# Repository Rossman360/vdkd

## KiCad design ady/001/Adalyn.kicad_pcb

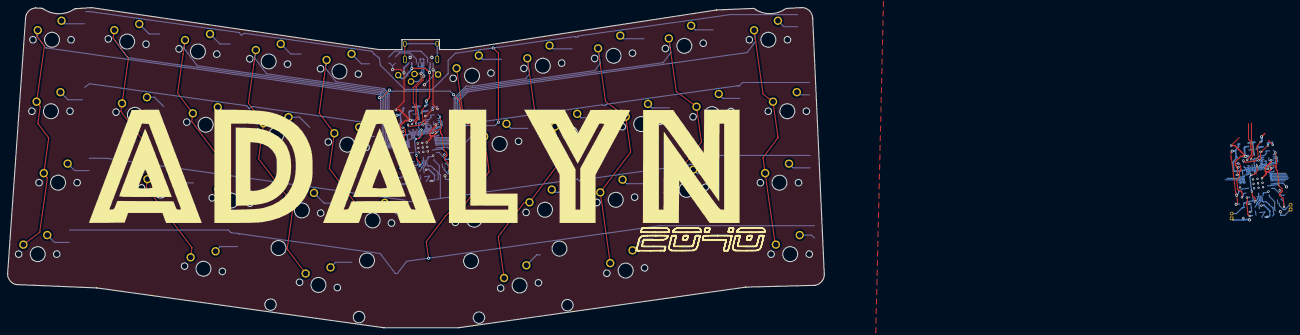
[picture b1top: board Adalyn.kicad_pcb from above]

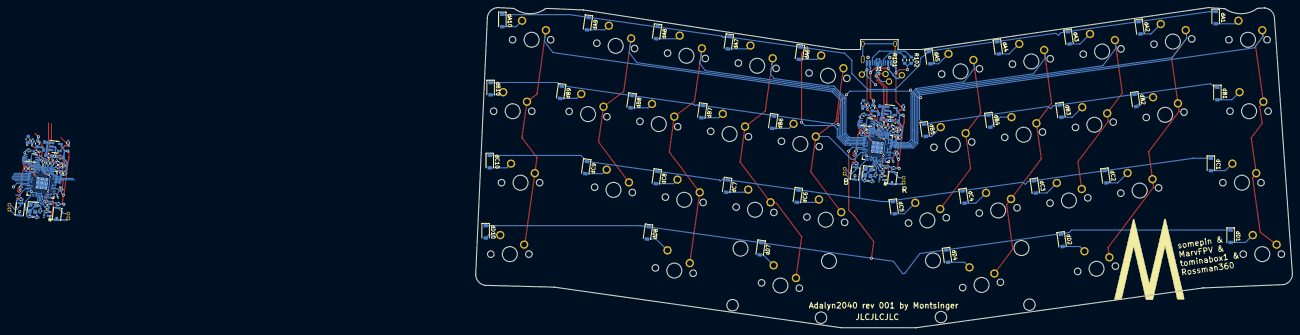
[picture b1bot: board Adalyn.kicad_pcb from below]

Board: 2 copper layers, 217.7 x 85.3 mm, 149 parts (109 on the bottom side), 89 nets.

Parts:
C1, C1#2, C2, C2#2: 1µ; C_0603_1608Metric
C3, C3#2, C4, C4#2: 15p; C_0402_1005Metric
C5, C5#2, C6, C6#2: 1µ; C_0402_1005Metric
C7, C7#2, C8, C8#2, C9, C9#2, C10, C10#2, C11, C11#2, C12, C12#2, C13, C13#2, C14, C14#2: 100n; C_0402_1005Metric
D1, D1#2: LED; LED_0402_1005Metric
D2, D2#2: B5817; D_SOD-323
F1, F1#2: Polyfuse; Fuse_0603_1608Metric
FB1, FB1#2: FerriteBead_Small; L_0603_1608Metric
J1: HRO-TYPE-C-31-M-12; HRO-TYPE-C-31-M-12-Assembly
J5, J5#2, J5#3, J5#4: Conn_01x02; PinHeader_1x02_P1.27mm_Vertical
R1, R1#2, R3, R3#2, R8, R8#2: 1k; R_0402_1005Metric
R2, R2#2, R9, R9#2, R11, R11#2: 10k; R_0402_1005Metric
R4, R4#2, R5, R5#2, R10, R10#2: 5.1k; R_0402_1005Metric
R6, R6#2, R7, R7#2: 27; R_0402_1005Metric
R101, R102: 5.1k; R_0603_1608Metric
SW1, SW1#2, SW2, SW2#2: SW_Push; SW_SPST_CK_KXT3
U1, U1#2: RP2040; QFN-56-1EP_7x7mm_P0.4mm_EP3.2x3.2mm
U2: GD25Q80CEIGR; USON-8-1EP_3x2mm_P0.5mm_EP0.25x1.65mm
U2#2: GD25Q80CEIGR; flash-chip
U3, U3#2: XC6210B332MR-G; SOT-23-5
Y1, Y1#2: Crystal_GND24; Crystal_SMD_2520-4Pin_2.5x2.0mm
dA1, dA2, dA3, dA4, dA5, dA6, dA7, dA8, dA9, dA10: Diode; diode_smd
dB1, dB2, dB3, dB4, dB5, dB6, dB7, dB8, dB9, dB10: Diode; diode_smd
dC1, dC2, dC3, dC4, dC5, dC6, dC7, dC8, dC9, dC10: Diode; diode_smd
dD1, dD2, dD4, dD7, dD8, dD10: Diode; diode_smd
kA1, kA2, kA3, kA4, kA5, kA6, kA7, kA8, kA9, kA10: MX-NoLED; MXOnly-1U-NoLED
kB1, kB2, kB3, kB4, kB5, kB6, kB7, kB8, kB9, kB10: MX-NoLED; MXOnly-1U-NoLED
kC1, kC2, kC3, kC4, kC5, kC6, kC7, kC8, kC9, kC10: MX-NoLED; MXOnly-1U-NoLED
kD1, kD2, kD8, kD10: MX-NoLED; MXOnly-1U-NoLED
kD4: MX-NoLED; MXOnly-2.25U-ReversedStabilizers-NoLED
kD7: MX-NoLED; MXOnly-2U-ReversedStabilizers-NoLED

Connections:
+1V1: C6.1, C6#2.1, C7.1, C7#2.1, C8.1, C8#2.1, U1.23 (DVDD), U1.45 (VREG_VOUT), U1.50 (DVDD), U1#2.23 (DVDD), U1#2.45 (VREG_VOUT), U1#2.50 (DVDD)
+3V3: C2.1, C2#2.1, C5.1, C5#2.1, C9.1, C9#2.1, C10.1, C10#2.1, C11.1, C11#2.1, C12.1, C12#2.1, C13.1, C13#2.1, C14.1, C14#2.1, R2.2, R2#2.2, R9.2, R9#2.2, U1.1 (IOVDD), U1.10 (IOVDD), U1.22 (IOVDD), U1.33 (IOVDD), U1.42 (IOVDD), U1.43 (ADC_AVDD), U1.44 (VREG_IN), U1.48 (USB_VDD), U1.49 (IOVDD), U1#2.1 (IOVDD), U1#2.10 (IOVDD), U1#2.22 (IOVDD), U1#2.33 (IOVDD), U1#2.42 (IOVDD), U1#2.43 (ADC_AVDD), U1#2.44 (VREG_IN), U1#2.48 (USB_VDD), U1#2.49 (IOVDD), U2.8 (VCC), U2#2.8 (VCC), U3.5 (VOUT), U3#2.5 (VOUT)
+5V: C1.1, C1#2.1, D2.1 (K), D2#2.1 (K), U3.1 (VIN), U3.3 (EN), U3#2.1 (VIN), U3#2.3 (EN)
/D6: U1.8 (GPIO6), U1#2.8 (GPIO6)
/D8: U1.11 (GPIO8), U1#2.11 (GPIO8)
/D13: U1.16 (GPIO13), U1#2.16 (GPIO13)
/D14: U1.17 (GPIO14), U1#2.17 (GPIO14)
/D15: U1.18 (GPIO15), U1#2.18 (GPIO15)
/D16: U1.27 (GPIO16), U1#2.27 (GPIO16)
/D21: U1.32 (GPIO21), U1#2.32 (GPIO21)
/LED: D1.2 (A), D1#2.2 (A), U1.28 (GPIO17), U1#2.28 (GPIO17)
/MISO: U1.31 (GPIO20), U1#2.31 (GPIO20)
/MOSI: U1.35 (GPIO23), U1#2.35 (GPIO23)
/QSPI_D0: U1.53 (QSPI_SD0), U1#2.53 (QSPI_SD0), U2.5 (DI(IO0)), U2#2.5 (DI(IO0))
/QSPI_D1: U1.55 (QSPI_SD1), U1#2.55 (QSPI_SD1), U2.2 (DO(IO1)), U2#2.2 (DO(IO1))
/QSPI_D2: U1.54 (QSPI_SD2), U1#2.54 (QSPI_SD2), U2.3 (IO2), U2#2.3 (IO2)
/QSPI_D3: U1.51 (QSPI_SD3), U1#2.51 (QSPI_SD3), U2.7 (IO3), U2#2.7 (IO3)
/QSPI_SCLK: U1.52 (QSPI_SCLK), U1#2.52 (QSPI_SCLK), U2.6 (CLK), U2#2.6 (CLK)
/QSPI_~CS: R3.2, R3#2.2, R9.1, R9#2.1, U1.56 (QSPI_SS), U1#2.56 (QSPI_SS), U2.1 (~CS), U2#2.1 (~CS)
/SCLK: U1.34 (GPIO22), U1#2.34 (GPIO22)
/VBUS_DET: R10.1, R10#2.1, R11.2, R11#2.2, U1.30 (GPIO19), U1#2.30 (GPIO19)
/~RESET: J5.2, J5#2.2, R2.1, R2#2.1, SW1.2, SW1#2.2, U1.26 (RUN/~RST), U1#2.26 (RUN/~RST)
CC1: J1.4, R101.2
CC2: J1.10, R102.1
D+: J1.6, J1.8, R6.1, R6#2.1
D-: J1.5, J1.7, R7.1, R7#2.1
GND: C1.2, C1#2.2, C2.2, C2#2.2, C3.2, C3#2.2, C4.2, C4#2.2, C5.2, C5#2.2, C6.2, C6#2.2, C7.2, C7#2.2, C8.2, C8#2.2, C9.2, C9#2.2, C10.2, C10#2.2, C11.2, C11#2.2, C12.2, C12#2.2, C13.2, C13#2.2, C14.2, C14#2.2, FB1.1, FB1#2.1, J1.1, J1.12, J5.1, J5#2.1, J5#3.1, J5#4.1, R1.1, R1#2.1, R4.2, R4#2.2, R5.2, R5#2.2, R11.1, R11#2.1, R101.1, R102.2, SW1.1, SW1#2.1, SW2.1, SW2#2.1, U1.19 (TESTEN), U1.57 (GND), U1#2.19 (TESTEN), U1#2.57 (GND), U2.4 (GND), U2.9 (EP), U2#2.4 (GND), U2#2.9 (EP), U3.2 (GND), U3#2.2 (GND), Y1.2, Y1.4, Y1#2.2, Y1#2.4
unnamed: C4.1, C4#2.1, R8.1, R8#2.1, Y1.3, Y1#2.3
unnamed: D1.1 (K), D1#2.1 (K), R1.2, R1#2.2
unnamed: D2.2 (A), D2#2.2 (A), F1.2, F1#2.2
unnamed: R4.1, R4#2.1
unnamed: R5.1, R5#2.1
unnamed: FB1.2, FB1#2.2
unnamed: J5#3.2, J5#4.2, R3.1, R3#2.1, SW2.2, SW2#2.2
unnamed: R7.2, R7#2.2, U1.46 (USB_DM), U1#2.46 (USB_DM)
unnamed: R6.2, R6#2.2, U1.47 (USB_DP), U1#2.47 (USB_DP)
unnamed: C3.1, C3#2.1, U1.20 (XIN), U1#2.20 (XIN), Y1.1, Y1#2.1
unnamed: R8.2, R8#2.2, U1.21 (XOUT), U1#2.21 (XOUT)
unnamed: dA1.2 (A), kA1.2 (ROW)
unnamed: dA2.2 (A), kA2.2 (ROW)
unnamed: dA3.2 (A), kA3.2 (ROW)
unnamed: dA4.2 (A), kA4.2 (ROW)
unnamed: dA5.2 (A), kA5.2 (ROW)
unnamed: dA6.2 (A), kA6.2 (ROW)
unnamed: dA7.2 (A), kA7.2 (ROW)
unnamed: dA8.2 (A), kA8.2 (ROW)
unnamed: dA9.2 (A), kA9.2 (ROW)
unnamed: dA10.2 (A), kA10.2 (ROW)
unnamed: dB1.2 (A), kB1.2 (ROW)
unnamed: dB2.2 (A), kB2.2 (ROW)
unnamed: dB3.2 (A), kB3.2 (ROW)
unnamed: dB4.2 (A), kB4.2 (ROW)
unnamed: dB5.2 (A), kB5.2 (ROW)
unnamed: dB6.2 (A), kB6.2 (ROW)
unnamed: dB7.2 (A), kB7.2 (ROW)
unnamed: dB8.2 (A), kB8.2 (ROW)
unnamed: dB9.2 (A), kB9.2 (ROW)
unnamed: dB10.2 (A), kB10.2 (ROW)
unnamed: dC1.2 (A), kC1.2 (ROW)
unnamed: dC2.2 (A), kC2.2 (ROW)
unnamed: dC3.2 (A), kC3.2 (ROW)
unnamed: dC4.2 (A), kC4.2 (ROW)
unnamed: dC5.2 (A), kC5.2 (ROW)
unnamed: dC6.2 (A), kC6.2 (ROW)
unnamed: dC7.2 (A), kC7.2 (ROW)
unnamed: dC8.2 (A), kC8.2 (ROW)
unnamed: dC9.2 (A), kC9.2 (ROW)
unnamed: dC10.2 (A), kC10.2 (ROW)
unnamed: dD1.2 (A), kD1.2 (ROW)
unnamed: dD2.2 (A), kD2.2 (ROW)
unnamed: dD4.2 (A), kD4.2
unnamed: dD7.2 (A), kD7.2
unnamed: dD8.2 (A), kD8.2 (ROW)
unnamed: dD10.2 (A), kD10.2 (ROW)
VBUS: F1.1, F1#2.1, J1.2, J1.11, R10.2, R10#2.2
c1: U1.37 (GPIO25), U1#2.37 (GPIO25), kA1.1 (COL), kB1.1 (COL), kC1.1 (COL), kD1.1 (COL)
c2: U1.38 (GPIO26_ADC0), U1#2.38 (GPIO26_ADC0), kA2.1 (COL), kB2.1 (COL), kC2.1 (COL), kD2.1 (COL)
c3: U1.39 (GPIO27_ADC1), U1#2.39 (GPIO27_ADC1), kA3.1 (COL), kB3.1 (COL), kC3.1 (COL)
c4: U1.40 (GPIO28_ADC2), U1#2.40 (GPIO28_ADC2), kA4.1 (COL), kB4.1 (COL), kC4.1 (COL), kD4.1
c5: U1.41 (GPIO29_ADC3), U1#2.41 (GPIO29_ADC3), kA5.1 (COL), kB5.1 (COL), kC5.1 (COL)
c6: U1.12 (GPIO9), U1#2.12 (GPIO9), kA6.1 (COL), kB6.1 (COL), kC6.1 (COL)
c7: U1.2 (GPIO0), U1#2.2 (GPIO0), kA7.1 (COL), kB7.1 (COL), kC7.1 (COL), kD7.1
c8: U1.3 (GPIO1), U1#2.3 (GPIO1), kA8.1 (COL), kB8.1 (COL), kC8.1 (COL), kD8.1 (COL)
c9: U1.4 (GPIO2), U1#2.4 (GPIO2), kA9.1 (COL), kB9.1 (COL), kC9.1 (COL)
c10: U1.5 (GPIO3), U1#2.5 (GPIO3), kA10.1 (COL), kB10.1 (COL), kC10.1 (COL), kD10.1 (COL)
rA: U1.7 (GPIO5), U1#2.7 (GPIO5), dA1.1 (K), dA2.1 (K), dA3.1 (K), dA4.1 (K), dA5.1 (K), dA6.1 (K), dA7.1 (K), dA8.1 (K), dA9.1 (K), dA10.1 (K)
rB: U1.6 (GPIO4), U1#2.6 (GPIO4), dB1.1 (K), dB2.1 (K), dB3.1 (K), dB4.1 (K), dB5.1 (K), dB6.1 (K), dB7.1 (K), dB8.1 (K), dB9.1 (K), dB10.1 (K)
rC: U1.15 (GPIO12), U1#2.15 (GPIO12), dC1.1 (K), dC2.1 (K), dC3.1 (K), dC4.1 (K), dC5.1 (K), dC6.1 (K), dC7.1 (K), dC8.1 (K), dC9.1 (K), dC10.1 (K)
rD: U1.9 (GPIO7), U1#2.9 (GPIO7), dD1.1 (K), dD2.1 (K), dD4.1 (K), dD7.1 (K), dD8.1 (K), dD10.1 (K)

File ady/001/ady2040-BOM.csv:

Comment,Designator,Footprint,LCSC
51k,"R101,R102",R_0603_1608Metric,2,5.1k,~
diodes,"dC6,dB10,dA6,dB8,dC10,dB4,dA10,dD1,dC5,dC2,dD2,dC1,dD4,dB3,dD8,dC4,dA3,dC3,dC7,dB1,dB7,dA7,dA4,dB6,dB5,dA8,dC8,dD7,dA2,dA9,dC9,dA1,dA5,dD10,dB9,dB2",C64898,
usb,J1,HRO-TYPE-C-31-M-12-Assembly,C165948,~
1k,"R1,R3,R8",R_0402_1005Metric,C11702,~
B5817,D2,D_SOD-323,C123899
LED,D1,LED_0402_1005Metric,C130719
100n,"C10,C11,C12,C13,C14,C7,C8,C9",C_0402_1005Metric,C1525
15p,"C3,C4",C_0402_1005Metric,C1548
1µ,"C1,C2",C_0603_1608Metric,C19666
RP2040,U1,QFN-56-1EP_7x7mm_P0.4mm_EP3.2x3.2mm,C2040
Crystal_GND24,Y1,Crystal_SMD_2520-4Pin_2.5x2.0mm,C2149204
27,"R6,R7",R_0402_1005Metric,C25100
10k,"R11,R2,R9",R_0402_1005Metric,C25744
5.1k,"R10,R4,R5",R_0402_1005Metric,C25905
SW_Push,"SW1,SW2",SW_SPST_CK_KXT3,C319433
GD25Q80CEIGR,U2,USON-8-1EP_3x2mm_P0.5mm_EP0.25x1.65mm,C152596
1µ,"C5,C6",C_0402_1005Metric,C52923
Polyfuse,F1,Fuse_0603_1608Metric,C69679
XC6210B332MR-G,U3,SOT-23-5,C82942
FerriteBead_Small,FB1,L_0603_1608Metric,C98288

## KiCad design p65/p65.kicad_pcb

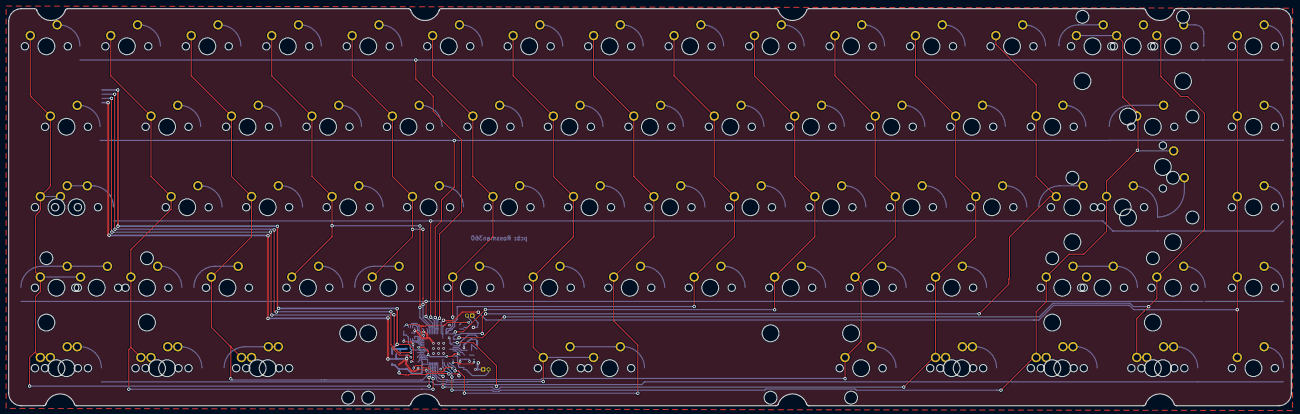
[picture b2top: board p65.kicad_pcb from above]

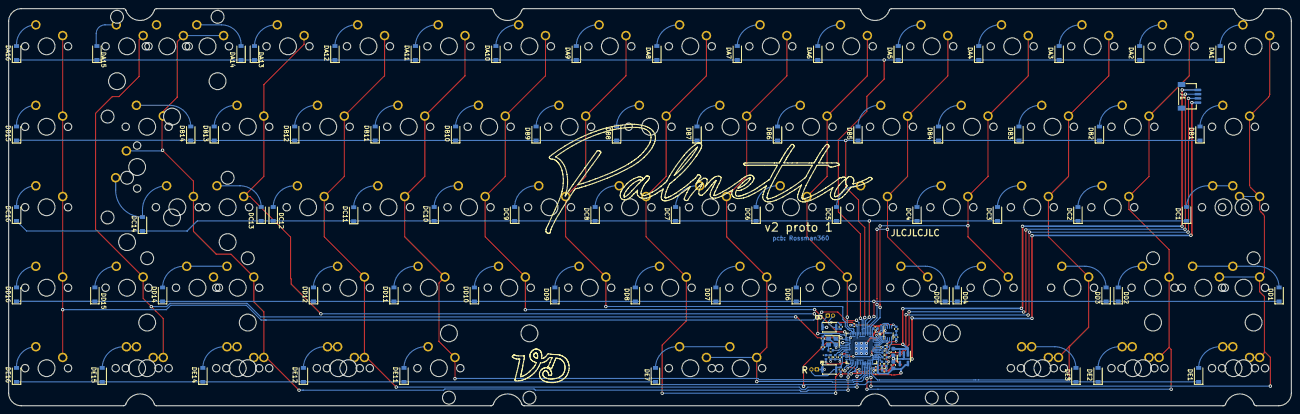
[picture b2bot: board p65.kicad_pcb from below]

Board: 2 copper layers, 303.7 x 94.0 mm, 185 parts (101 on the bottom side), 113 nets.

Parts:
C1, C2: 1µ; C_0603_1608Metric
C3, C4: 15p; C_0402_1005Metric
C5, C6: 1µ; C_0402_1005Metric
C7, C8, C9, C10, C11, C12, C13, C14: 100n; C_0402_1005Metric
D1: LED; LED_0402_1005Metric
DA1, DA2, DA3, DA4, DA5, DA6, DA7, DA8, DA9, DA10, DA11, DA12, DA13, DA14, DA15, DA16: Diode; diode_smd
DB1, DB2, DB3, DB4, DB5, DB6, DB7, DB8, DB9, DB10, DB11, DB12, DB13, DB14, DB15: Diode; diode_smd
DC1, DC2, DC3, DC4, DC5, DC6, DC7, DC8, DC9, DC10, DC11, DC12, DC13, DC14, DC16: Diode; diode_smd
DD1, DD2, DD3, DD4, DD5, DD6, DD7, DD8, DD9, DD10, DD11, DD12, DD14, DD15, DD16: Diode; diode_smd
DE1, DE2, DE3, DE7, DE11, DE12, DE14, DE15, DE16: Diode; diode_smd
J1: SM04B-SRSS-TB(LF)(SN); jst
J5, J5#2: Conn_01x02; PinHeader_1x02_P1.27mm_Vertical
KA1: Esc; MXOnly-1U-NoLED
KA2: 1; MXOnly-1U-NoLED
KA3: 2; MXOnly-1U-NoLED
KA4: 3; MXOnly-1U-NoLED
KA5: 4; MXOnly-1U-NoLED
KA6: 5; MXOnly-1U-NoLED
KA7: 6; MXOnly-1U-NoLED
KA8: 7; MXOnly-1U-NoLED
KA9: 8; MXOnly-1U-NoLED
KA10: 9; MXOnly-1U-NoLED
KA11: 10; MXOnly-1U-NoLED
KA12: -; MXOnly-1U-NoLED
KA13: =; MXOnly-1U-NoLED
KA14: Bspc; MXOnly-1U-NoLED
KA14.2: Bspc; MXOnly-2U-NoLED
KA15: `; MXOnly-1U-NoLED
KA16: del; MXOnly-1U-NoLED
KB1: Tab; MXOnly-1.5U-NoLED
KB2: Q; MXOnly-1U-NoLED
KB3: W; MXOnly-1U-NoLED
KB4: E; MXOnly-1U-NoLED
KB5: R; MXOnly-1U-NoLED
KB6: T; MXOnly-1U-NoLED
KB7: Y; MXOnly-1U-NoLED
KB8: U; MXOnly-1U-NoLED
KB9: I; MXOnly-1U-NoLED
KB10: O; MXOnly-1U-NoLED
KB11: P; MXOnly-1U-NoLED
KB12: [; MXOnly-1U-NoLED
KB13: ]; MXOnly-1U-NoLED
KB14: \; MXOnly-1.5U-NoLED
KB16: home; MXOnly-1U-NoLED
KC1: Caps; MXOnly-1.75U-NoLED
KC1.2: Stepped; MXOnly-1.25U-NoLED
KC2: A; MXOnly-1U-NoLED
KC3: S; MXOnly-1U-NoLED
KC4: D; MXOnly-1U-NoLED
KC5: F; MXOnly-1U-NoLED
KC6: G; MXOnly-1U-NoLED
KC7: H; MXOnly-1U-NoLED
KC8: J; MXOnly-1U-NoLED
KC9: K; MXOnly-1U-NoLED
KC10: L; MXOnly-1U-NoLED
KC11: ;; MXOnly-1U-NoLED
KC12: '; MXOnly-1U-NoLED
KC13: #; MXOnly-1U-NoLED
KC14: Enter; MXOnly-2.25U-NoLED
KC14.2: Enter; MXOnly-ISO-ROTATED-ReversedStabilizers-NoLED
KC16: pgup; MXOnly-1U-NoLED
KD1: Lshift; MXOnly-1.25U-NoLED
KD1.2: Lshift; MXOnly-2.25U-NoLED
KD2: \; MXOnly-1U-NoLED
KD3: Z; MXOnly-1U-NoLED
KD4: X; MXOnly-1U-NoLED
KD5: C; MXOnly-1U-NoLED
KD6: V; MXOnly-1U-NoLED
KD7: B; MXOnly-1U-NoLED
KD8: N; MXOnly-1U-NoLED
KD9: M; MXOnly-1U-NoLED
KD10: ,; MXOnly-1U-NoLED
KD11: .; MXOnly-1U-NoLED
KD12: /; MXOnly-1U-NoLED
KD14: Rsft; MXOnly-1.75U-NoLED
KD14.2: Rsft; MXOnly-2.75U-NoLED
KD15: Fn; MXOnly-1U-NoLED
KD16: pgdn; MXOnly-1U-NoLED
KE1: LCtl; MXOnly-1.25U-NoLED
KE1.2: LCtl; MXOnly-1.5U-NoLED
KE2: LWin; MXOnly-1.25U-NoLED
KE2.2: LWin; MXOnly-1U-NoLED
KE3: LAlt; MXOnly-1.25U-NoLED
KE3.2: LAlt; MXOnly-1.5U-NoLED
KE7: Space; MXOnly-6.25U-ReversedStabilizers-NoLED
KE7.2: Space; MXOnly-7U-ReversedStabilizers-NoLED
KE11: AltGr; MXOnly-1.25U-NoLED
KE12: Rwin; MXOnly-1.25U-NoLED
KE12.2: Rwin; MXOnly-1.5U-NoLED
KE14: RMenu; MXOnly-1.25U-NoLED
KE14.2: RMenu; MXOnly-1U-NoLED
KE15: Rctl; MXOnly-1.25U-NoLED
KE15.2: Rctl; MXOnly-1.5U-NoLED
KE16: Pgdn; MXOnly-1U-NoLED
R1, R3, R8: 1k; R_0402_1005Metric
R2, R9, R11: 10k; R_0402_1005Metric
R6, R7: 27; R_0402_1005Metric
R10: 5.1k; R_0402_1005Metric
SW1, SW2: SW_Push; SW_SPST_CK_KXT3
U1: RP2040; QFN-56-1EP_7x7mm_P0.4mm_EP3.2x3.2mm
U2: GD25Q80CEIGR; USON-8-1EP_3x2mm_P0.5mm_EP0.25x1.65mm
U3: XC6210B332MR-G; SOT-23-5
Y1: Crystal_GND24; Crystal_SMD_2520-4Pin_2.5x2.0mm

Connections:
+1V1: C6.1, C7.1, C8.1, U1.23 (DVDD), U1.45 (VREG_VOUT), U1.50 (DVDD)
+3V3: C2.1, C5.1, C9.1, C10.1, C11.1, C12.1, C13.1, C14.1, R2.2, R9.2, U1.1 (IOVDD), U1.10 (IOVDD), U1.22 (IOVDD), U1.33 (IOVDD), U1.42 (IOVDD), U1.43 (ADC_AVDD), U1.44 (VREG_IN), U1.48 (USB_VDD), U1.49 (IOVDD), U2.8 (VCC), U3.5 (VOUT)
+5V: C1.1, J1.1, R10.2, U3.1 (VIN), U3.3 (EN)
/LED: D1.2 (A), U1.28 (GPIO17)
/QSPI_D0: U1.53 (QSPI_SD0), U2.5 (DI(IO0))
/QSPI_D1: U1.55 (QSPI_SD1), U2.2 (DO(IO1))
/QSPI_D2: U1.54 (QSPI_SD2), U2.3 (IO2)
/QSPI_D3: U1.51 (QSPI_SD3), U2.7 (IO3)
/QSPI_SCLK: U1.52 (QSPI_SCLK), U2.6 (CLK)
/QSPI_~CS: R3.2, R9.1, U1.56 (QSPI_SS), U2.1 (~CS)
/VBUS_DET: R10.1, R11.2, U1.30 (GPIO19)
/~RESET: R2.1, SW1.2, U1.26 (RUN/~RST)
D+: J1.3, R6.1
D-: J1.2, R7.1
GND: C1.2, C2.2, C3.2, C4.2, C5.2, C6.2, C7.2, C8.2, C9.2, C10.2, C11.2, C12.2, C13.2, C14.2, J1.4, J5.1, J5#2.1, R1.1, R11.1, SW1.1, SW2.1, U1.19 (TESTEN), U1.57 (GND), U2.4 (GND), U2.9 (EP), U3.2 (GND), Y1.2, Y1.4
unnamed: C4.1, R8.1, Y1.3
unnamed: D1.1 (K), R1.2
unnamed: DA1.2 (A), KA1.2 (Row)
unnamed: DA2.2 (A), KA2.2 (Row)
unnamed: DA3.2 (A), KA3.2 (Row)
unnamed: DA4.2 (A), KA4.2 (Row)
unnamed: DA5.2 (A), KA5.2 (Row)
unnamed: DA6.2 (A), KA6.2 (Row)
unnamed: DA7.2 (A), KA7.2 (Row)
unnamed: DA8.2 (A), KA8.2 (Row)
unnamed: DA9.2 (A), KA9.2 (Row)
unnamed: DA10.2 (A), KA10.2 (Row)
unnamed: DA11.2 (A), KA11.2 (Row)
unnamed: DA12.2 (A), KA12.2 (Row)
unnamed: DA13.2 (A), KA13.2 (Row)
unnamed: DA14.2 (A), KA14.2 (Row), KA14.2.2 (Row)
unnamed: DA15.2 (A), KA15.2 (Row)
unnamed: DA16.2 (A), KA16.2 (Row)
unnamed: DB1.2 (A), KB1.2 (Row)
unnamed: DB2.2 (A), KB2.2 (Row)
unnamed: DB3.2 (A), KB3.2 (Row)
unnamed: DB4.2 (A), KB4.2 (Row)
unnamed: DB5.2 (A), KB5.2 (Row)
unnamed: DB6.2 (A), KB6.2 (Row)
unnamed: DB7.2 (A), KB7.2 (Row)
unnamed: DB8.2 (A), KB8.2 (Row)
unnamed: DB9.2 (A), KB9.2 (Row)
unnamed: DB10.2 (A), KB10.2 (Row)
unnamed: DB11.2 (A), KB11.2 (Row)
unnamed: DB12.2 (A), KB12.2 (Row)
unnamed: DB13.2 (A), KB13.2 (Row)
unnamed: DB14.2 (A), KB14.2 (Row)
unnamed: DB15.2 (A), KB16.2 (Row)
unnamed: DC1.2 (A), KC1.2 (Row), KC1.2.2 (Row)
unnamed: DC2.2 (A), KC2.2 (Row)
unnamed: DC3.2 (A), KC3.2 (Row)
unnamed: DC4.2 (A), KC4.2 (Row)
unnamed: DC5.2 (A), KC5.2 (Row)
unnamed: DC6.2 (A), KC6.2 (Row)
unnamed: DC7.2 (A), KC7.2 (Row)
unnamed: DC8.2 (A), KC8.2 (Row)
unnamed: DC9.2 (A), KC9.2 (Row)
unnamed: DC10.2 (A), KC10.2 (Row)
unnamed: DC11.2 (A), KC11.2 (Row)
unnamed: DC12.2 (A), KC12.2 (Row)
unnamed: DC13.2 (A), KC13.2 (Row)
unnamed: DC14.2 (A), KC14.2 (Row), KC14.2.2 (Row)
unnamed: DC16.2 (A), KC16.2 (Row)
unnamed: DD1.2 (A), KD1.2 (Row), KD1.2.2 (Row)
unnamed: DD2.2 (A), KD2.2 (Row)
unnamed: DD3.2 (A), KD3.2 (Row)
unnamed: DD4.2 (A), KD4.2 (Row)
unnamed: DD5.2 (A), KD5.2 (Row)
unnamed: DD6.2 (A), KD6.2 (Row)
unnamed: DD7.2 (A), KD7.2 (Row)
unnamed: DD8.2 (A), KD8.2 (Row)
unnamed: DD9.2 (A), KD9.2 (Row)
unnamed: DD10.2 (A), KD10.2 (Row)
unnamed: DD11.2 (A), KD11.2 (Row)
unnamed: DD12.2 (A), KD12.2 (Row)
unnamed: DD14.2 (A), KD14.2 (Row), KD14.2.2 (Row)
unnamed: DD15.2 (A), KD15.2 (Row)
unnamed: DD16.2 (A), KD16.2 (Row)
unnamed: DE1.2 (A), KE1.2 (Row), KE1.2.2 (Row)
unnamed: DE2.2 (A), KE2.2 (Row), KE2.2.2 (Row)
unnamed: DE3.2 (A), KE3.2 (Row), KE3.2.2 (Row)
unnamed: DE7.2 (A), KE7.2 (Row), KE7.2.2 (Row)
unnamed: DE11.2 (A), KE11.2 (Row)
unnamed: DE12.2 (A), KE12.2 (Row), KE12.2.2 (Row)
unnamed: DE14.2 (A), KE14.2 (Row), KE14.2.2 (Row)
unnamed: DE15.2 (A), KE15.2 (Row), KE15.2.2 (Row)
unnamed: DE16.2 (A), KE16.2 (Row)
unnamed: J5.2, J5#2.2, R3.1, SW2.2
unnamed: R7.2, U1.46 (USB_DM)
unnamed: R6.2, U1.47 (USB_DP)
unnamed: C3.1, U1.20 (XIN), Y1.1
unnamed: R8.2, U1.21 (XOUT)
c1: KA1.1 (Col), KB1.1 (Col), KC1.1 (Col), KC1.2.1 (Col), KD1.1 (Col), KD1.2.1 (Col), KE1.1 (Col), KE1.2.1 (Col), U1.40 (GPIO28_ADC2)
c2: KA2.1 (Col), KB2.1 (Col), KC2.1 (Col), KD2.1 (Col), KE2.1 (Col), KE2.2.1 (Col), U1.39 (GPIO27_ADC1)
c3: KA3.1 (Col), KB3.1 (Col), KC3.1 (Col), KD3.1 (Col), KE3.1 (Col), KE3.2.1 (Col), U1.41 (GPIO29_ADC3)
c4: KA4.1 (Col), KB4.1 (Col), KC4.1 (Col), KD4.1 (Col), U1.2 (GPIO0)
c5: KA5.1 (Col), KB5.1 (Col), KC5.1 (Col), KD5.1 (Col), U1.3 (GPIO1)
c6: KA6.1 (Col), KB6.1 (Col), KC6.1 (Col), KD6.1 (Col), U1.12 (GPIO9)
c7: KA7.1 (Col), KB7.1 (Col), KC7.1 (Col), KD7.1 (Col), KE7.1 (Col), KE7.2.1 (Col), U1.38 (GPIO26_ADC0)
c8: KA8.1 (Col), KB8.1 (Col), KC8.1 (Col), KD8.1 (Col), U1.29 (GPIO18)
c9: KA9.1 (Col), KB9.1 (Col), KC9.1 (Col), KD9.1 (Col), U1.13 (GPIO10)
c10: KA10.1 (Col), KB10.1 (Col), KC10.1 (Col), KD10.1 (Col), U1.14 (GPIO11)
c11: KA11.1 (Col), KB11.1 (Col), KC11.1 (Col), KD11.1 (Col), KE11.1 (Col), U1.37 (GPIO25)
c12: KA12.1 (Col), KB12.1 (Col), KC12.1 (Col), KD12.1 (Col), KE12.1 (Col), KE12.2.1 (Col), U1.36 (GPIO24)
c13: KA13.1 (Col), KB13.1 (Col), KC13.1 (Col), U1.15 (GPIO12)
c14: KA14.1 (Col), KA14.2.1 (Col), KB14.1 (Col), KC14.1 (Col), KC14.2.1 (Col), KD14.1 (Col), KD14.2.1 (Col), KE14.1 (Col), KE14.2.1 (Col), U1.32 (GPIO21)
c15: KA15.1 (Col), KD15.1 (Col), KE15.1 (Col), KE15.2.1 (Col), U1.16 (GPIO13)
c16: KA16.1 (Col), KB16.1 (Col), KC16.1 (Col), KD16.1 (Col), KE16.1 (Col), U1.9 (GPIO7)
rA: DA1.1 (K), DA2.1 (K), DA3.1 (K), DA4.1 (K), DA5.1 (K), DA6.1 (K), DA7.1 (K), DA8.1 (K), DA9.1 (K), DA10.1 (K), DA11.1 (K), DA12.1 (K), DA13.1 (K), DA14.1 (K), DA15.1 (K), DA16.1 (K), U1.7 (GPIO5)
rB: DB1.1 (K), DB2.1 (K), DB3.1 (K), DB4.1 (K), DB5.1 (K), DB6.1 (K), DB7.1 (K), DB8.1 (K), DB9.1 (K), DB10.1 (K), DB11.1 (K), DB12.1 (K), DB13.1 (K), DB14.1 (K), DB15.1 (K), U1.6 (GPIO4)
rC: DC1.1 (K), DC2.1 (K), DC3.1 (K), DC4.1 (K), DC5.1 (K), DC6.1 (K), DC7.1 (K), DC8.1 (K), DC9.1 (K), DC10.1 (K), DC11.1 (K), DC12.1 (K), DC13.1 (K), DC14.1 (K), DC16.1 (K), U1.5 (GPIO3)
rD: DD1.1 (K), DD2.1 (K), DD3.1 (K), DD4.1 (K), DD5.1 (K), DD6.1 (K), DD7.1 (K), DD8.1 (K), DD9.1 (K), DD10.1 (K), DD11.1 (K), DD12.1 (K), DD14.1 (K), DD15.1 (K), DD16.1 (K), U1.4 (GPIO2)
rE: DE1.1 (K), DE2.1 (K), DE3.1 (K), DE7.1 (K), DE11.1 (K), DE12.1 (K), DE14.1 (K), DE15.1 (K), DE16.1 (K), U1.18 (GPIO15)

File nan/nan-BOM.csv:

Comment,Designator,Footprint,LCSC
LED,D1,LED_0402_1005Metric,C130719
diodes,"DE7,DB6,DB2,DE15,DD1,DA15,DB4,DC9,DA5,DA11,DB11,DD7,DB14,DD14,DD10,DD12,DD15,DA6,DE14,DB5,DC3,DC8,DB12,DA8,DA13,DD4,DD3,DC13,DC6,DD5,DC11,DA2,DC2,DD9,DE12,DC7,DA3,DB13,DA1,DD11,DA9,DC4,DA4,DC5,DA12,DE3,DB1,DD8,DE2,DE1,DB7,DC10,DD2,DC12,DC14,DD6,DB9,DE11,DB10,DB3,DB8,DA7,DA10,DA14,DC1",C64898
1µ,"C5,C6",C_0402_1005Metric,C52923
GD25Q80CEIGR,U2,USON-8-1EP_3x2mm_P0.5mm_EP0.25x1.65mm,C152596
SW_Push,"SW1,SW2",SW_SPST_CK_KXT3,C319433
15p,"C3,C4",C_0402_1005Metric,C1548
1µ,"C1,C2",C_0603_1608Metric,C19666
JST,J1,SM04B-SRSS-TB(LF)(SN),C160404
10k,"R11,R2,R9",R_0402_1005Metric,C25744
100n,"C10,C11,C12,C13,C14,C7,C8,C9",C_0402_1005Metric,C1525
Crystal_GND24,Y1,Crystal_SMD_2520-4Pin_2.5x2.0mm,C2149204
XC6210B332MR-G,U3,SOT-23-5,C82942
5.1k,"R10",R_0402_1005Metric,C25905
1k,"R1,R3,R8",R_0402_1005Metric,C11702,~
27,"R6,R7",R_0402_1005Metric,C25100
RP2040,U1,QFN-56-1EP_7x7mm_P0.4mm_EP3.2x3.2mm,C2040

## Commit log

2024-05-21 init commit
2024-05-26 including madeline
